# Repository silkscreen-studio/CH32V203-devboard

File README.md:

# CH32V203 devboard

A simple CH32V203C8U6 devboard, with a 7x8 charlieplexed matrix and a 12P FPC for IOs, beside the more common 2.54 headers for breadboard compatibility.
<br></br>

# Key features 
 - CH32V203C8U6 MCU:
    - FLASH: 64k (+224K non-zero-wait program memory)
    - SRAM: 20k
    - 144MHz CPU max clock speed
    - 37 GPIOs
    - Many peripherals (4x USART, 2x SPI, 2x I2C, 1x CAN, USB (FS))
    - 9 analog capable GPIOs
    - 12 PWM capable GPIOs
 - USB-C for programming, USB device/host emulation, and power
 - 7x8 charlieplexed LED matrix (8 GPIOs)
 - 23x 2.54mm header pins
 - 12P .5mm FPC for breaking out 9 more IOs
 - Boot and Reset Button
 - On board 3.3V LDO `TLV75733PDBVR`, 1A max current

Demo with the charlieplexed LED matrix in action:
https://youtube.com/shorts/uVbg5wJzLvo
<br></br>

<br></br>

# Schematic

<br></br>

# PCB layout

<br></br>

# Pinout

<br></br>

# BOM

| Qty | Type | Part | Value | Extended description | Unit price | Price [MOQ]| LCSC part number | Link |
| --- | --- | --- | --- | --- | --- | --- | --- | --- |
| 7 | MLCC | CL05B104KB54PNC | 100nF | 0402 | $0.014 | $1.40 [100] | C307331 | https://www.lcsc.com/product-detail/C307331.html |
| 3 | MLCC | CL10A106MA8NRNC | 10µF | 0603 | $0.14 | $2.80 [20] | C96446 | https://www.lcsc.com/product-detail/C96446.html |
| 1 | Ideal Diode | CH213K | |  | $0.074 | $0.74 [10] | C5456874 | https://www.lcsc.com/product-detail/C5456874.html |
| 1 | FPC connector 12P | FPC-05F-12PH20 | |  | $0.11 | $0.57 [5] | C2856799 | https://www.lcsc.com/product-detail/C2856799.html |
| 56 | LED | XL-1005UOC | | Orange 0402 LED | $0.014 | $1.42 [100] | C965791 | https://www.lcsc.com/product-detail/C965791.html |
| 3 | Resistor | RC0402JR-7W10KL | 10k | 0402 SMD resistor | $0.004 | $0.45 [100] | C851859 | https://www.lcsc.com/product-detail/C851859.html |
| 2 | Resistor | RC-02K512JT | 5.1k | 0402 SMD resistor | $0.0033 | $0.33 [100] | C453708 | https://www.lcsc.com/product-detail/C453708.html |
| 8 | Resistor | RC0402FR-07680RL | 680 | 0402 SMD resistor | $0.0014 | $0.14 [100] | C137948 | https://www.lcsc.com/product-detail/C137948.html |
| 2 | Push button | TS-1075S-A1B2-D4 | | | $0.066 | $0.66 [10] | C492872 | https://www.lcsc.com/product-detail/C492872.html |
| 1 | MCU | CH32V203C8U6 | | | $0.85 | $0.85 [1] | C6407762 | https://www.lcsc.com/product-detail/C6407762.html |
| 1 | LDO | TLV75733PDBVR | | 3.3V LDO | $0.18 | $0.92 [5] | C485517 | https://www.lcsc.com/product-detail/C485517.html |
| 1 | ESD protection | USBLC6-2P6 | | | $0.28 | $1.39 [5] | C15999 | https://www.lcsc.com/product-detail/C15999.html |
| 1 | PCB | | | | $5 |  |  | https://jlcpcb.com/quote |
|  |  |  |  |  |  |  |  |  |
|  | TOTAL (price per board) | | | | $7.96 |  |  |  |
|  | TOTAL (price due to MOQ) | | | | $16.67 |  |  |  |

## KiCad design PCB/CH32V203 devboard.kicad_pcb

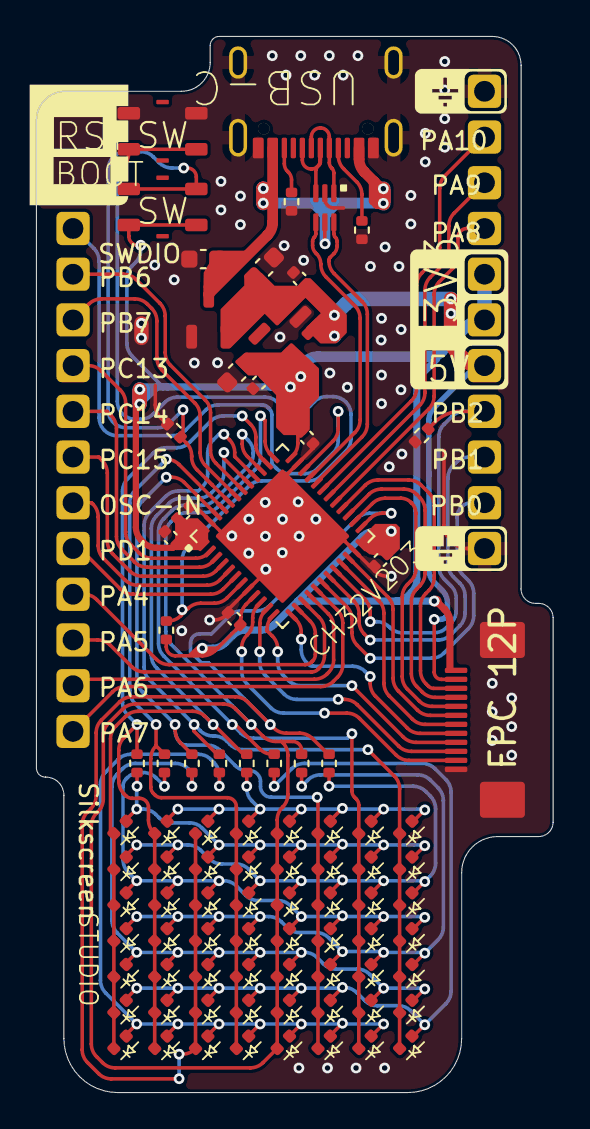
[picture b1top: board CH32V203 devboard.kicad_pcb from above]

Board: 2 copper layers, 28.7 x 58.7 mm, 110 parts (0 on the bottom side), 55 nets.

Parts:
C1, C2, C3, C4, C5, C6, C9: 100nF; C_0402_1005Metric
C7, C8, C10: 10uF; C_0603_1608Metric
D1: SOT-23-3
FPC1: FPC 12P Custom footprint C2856799
J1: USB C connector USB2.0 16P; USB_C_16P_custom_footprint_C2765186
LED2, LED3, LED4, LED5, LED6, LED7, LED8, LED9, LED11, LED12, LED13, LED14, LED15, LED16, LED17, LED18, LED20, LED21, LED22, LED23, LED24, LED25, LED26, LED27, LED29, LED30, LED31, LED32, LED33, LED34, LED35, LED36, LED38, LED39, LED40, LED41, LED42, LED43, LED44, LED45, LED47, LED48, LED49, LED50, LED51, LED52, LED53, LED54, LED56, LED57, LED58, LED59, LED60, LED61, LED62, LED63: LED; CUSTOM LED_0402_1005Metric
P1, P2, P3, P4, P5, P6, P7, P8, P9, P10, P12, P13, P18, P19, P20, P21, P22, P23, P26, P27, P28, P29, P30: Custom 1P 2.54mm header
R1, R2, R3: 10k; R_0402_1005Metric
R4, R5: 5.1k; R_0402_1005Metric
R6, R7, R8, R9, R10, R11, R12, R13: 680; R_0402_1005Metric
SW1, SW2: SW_Push; switch_custom_footprint_TS-1075S-A1B2-D4_C492872.pretty
U1: CUSTOM_QFN-48-1EP_7x7mm_P0.5mm_EP5.3x5.3mm
U2: SOT-23-5
U3: USBLC6-2P6; USB ESD SOT666 C15999

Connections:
+3.3V: C1.1, C2.1, C3.1, C4.1, C5.1, C8.1, C9.1, FPC1.1, P18.1, P19.1, R1.1, SW2.2, U1.1 (VBAT), U1.9 (VDDA), U1.24 (VDD_VIO_1), U1.36 (VDD_2), U1.48 (VDD_VIO_3), U2.5 (OUT)
+5V: C6.1, C7.1, D1.2 (OUT+), FPC1.2, P20.1, U2.1 (IN), U2.3 (EN)
/USB.VBUS: C10.1, D1.3 (IN+), J1.VBUS (VBUS_VBUS), U3.5 (VBUS)
GND: C1.2, C2.2, C3.2, C4.2, C5.2, C6.2, C7.2, C8.2, C9.2, C10.2, D1.1 (GND), FPC1.12, FPC1.13 (SH1), FPC1.14 (SH2), J1.GND (GND_GND), J1.SHIELD (SHIELD_SH), P12.1, P13.1, R2.2, R3.2, R4.2, R5.2, SW1.1, U1.8 (VSSA), U1.23 (VSS_1), U1.35 (VSS_2), U1.47 (VSS_3), U1.49 (VSS), U2.2 (GND), U3.2 (GND)
unnamed: J1.CC1 (CC1_CC1), R5.1
unnamed: J1.CC2 (CC2_CC2), R4.1
unnamed: J1.D+ (D+_D+), U3.3 (I/O2)
unnamed: J1.D- (D-_D-), U3.1 (I/O1)
unnamed: LED3.2 (A), LED11.2 (A), LED27.2 (A), LED35.2 (A), LED43.2 (A), LED51.2 (A), LED59.2 (A), R8.2
unnamed: LED4.2 (A), LED12.2 (A), LED20.2 (A), LED36.2 (A), LED44.2 (A), LED52.2 (A), LED60.2 (A), R9.2
unnamed: LED5.2 (A), LED13.2 (A), LED21.2 (A), LED29.2 (A), LED45.2 (A), LED53.2 (A), LED61.2 (A), R10.2
unnamed: LED6.2 (A), LED14.2 (A), LED22.2 (A), LED30.2 (A), LED38.2 (A), LED54.2 (A), LED62.2 (A), R11.2
unnamed: LED7.2 (A), LED15.2 (A), LED23.2 (A), LED31.2 (A), LED39.2 (A), LED47.2 (A), LED63.2 (A), R12.2
unnamed: LED8.2 (A), LED16.2 (A), LED24.2 (A), LED32.2 (A), LED40.2 (A), LED48.2 (A), LED56.2 (A), R13.2
unnamed: LED9.2 (A), LED17.2 (A), LED25.2 (A), LED33.2 (A), LED41.2 (A), LED49.2 (A), LED57.2 (A), R6.2
unnamed: LED2.2 (A), LED18.2 (A), LED26.2 (A), LED34.2 (A), LED42.2 (A), LED50.2 (A), LED58.2 (A), R7.2
unnamed: R2.1, SW2.1, U1.44 (BOOT0)
unnamed: R1.2, SW1.2, U1.7 (NRST)
OSC_IN: P4.1, U1.5 (OSC_IN/PD0)
PA0: FPC1.11, U1.10 (PA0/WKUP/ADC0/TIM2_CH1)
PA1: FPC1.10, U1.11 (PA1/ADC1/TIM2_CH2)
PA2: FPC1.9, U1.12 (PA2/ADC2/TIM2_CH3/TX2)
PA3: FPC1.8, U1.13 (PA3/ADC3/TIM2_CH4/RX2)
PA4: P6.1, U1.14 (PA4/ADC4)
PA5: P7.1, U1.15 (PA5/ADC5/SPI1_SCK)
PA6: P8.1, U1.16 (PA6/ADC6/SPI1_MISO/TIM3_CH1)
PA7: P9.1, U1.17 (PA7/ADC7/SPI1_MOSI/TIM3_CH2)
PA8: P26.1, U1.29 (TIM1_CH1/PA8)
PA9: P27.1, U1.30 (TX1/TIM1_CH2/PA9)
PA10: P28.1, U1.31 (RX1/TIM1_CH3/PA10)
PA14: LED33.1 (K), LED34.1 (K), LED35.1 (K), LED36.1 (K), LED38.1 (K), LED39.1 (K), LED40.1 (K), R10.1, U1.37 (SWCLK/PA14)
PA15: LED9.1 (K), LED11.1 (K), LED12.1 (K), LED13.1 (K), LED14.1 (K), LED15.1 (K), LED16.1 (K), R7.1, U1.38 (PA15)
PB0: P21.1, U1.18 (PB0/ADC8/TIM3_CH3/TX4)
PB1: P22.1, U1.19 (PB1/ADC9/TIM3_CH4/RX4)
PB2/BOOT1: P10.1, R3.1, U1.20 (PB2/BOOT1)
PB3: LED49.1 (K), LED50.1 (K), LED51.1 (K), LED52.1 (K), LED53.1 (K), LED54.1 (K), LED56.1 (K), R12.1, U1.39 (PB3)
PB4: LED57.1 (K), LED58.1 (K), LED59.1 (K), LED60.1 (K), LED61.1 (K), LED62.1 (K), LED63.1 (K), R13.1, U1.40 (PB4)
PB5: LED2.1 (K), LED3.1 (K), LED4.1 (K), LED5.1 (K), LED6.1 (K), LED7.1 (K), LED8.1 (K), R6.1, U1.41 (PB5)
PB6: P29.1, U1.42 (TIM4_CH1/SCL1/PB6/USB2DM)
PB7: P30.1, U1.43 (TIM4_CH2/SDA1/PB7/USB2DP)
PB8: LED25.1 (K), LED26.1 (K), LED27.1 (K), LED29.1 (K), LED30.1 (K), LED31.1 (K), LED32.1 (K), R9.1, U1.45 (TIM4_CH3/PB8)
PB9: LED41.1 (K), LED42.1 (K), LED43.1 (K), LED44.1 (K), LED45.1 (K), LED47.1 (K), LED48.1 (K), R11.1, U1.46 (TIM4_CH4/PB9)
PB10: FPC1.7, U1.21 (PB10/SCL2/TX3)
PB11: FPC1.6, U1.22 (PB11/SDA2/RX3)
PB12: LED17.1 (K), LED18.1 (K), LED20.1 (K), LED21.1 (K), LED22.1 (K), LED23.1 (K), LED24.1 (K), R8.1, U1.25 (PB12)
PB13: FPC1.5, U1.26 (SPI2_SCK/PB13)
PB14: FPC1.4, U1.27 (SPI2_MISO/PB14)
PB15: FPC1.3, U1.28 (SPI2_MOSI/PB15)
PC13: P1.1, U1.2 (PC13/TAMPER_RTC)
PC14: P2.1, U1.3 (PC14/OSC32IN)
PC15: P3.1, U1.4 (PC15/OSC32OUT)
PD1: P5.1, U1.6 (OSC_OUT/PD1)
SWDIO: P23.1, U1.34 (SWDIO/PA13)
USB.D+: U1.33 (CAN_TX1/PA12/USB1DP), U3.4 (I/O2)
USB.D-: U1.32 (TIM1_CH4/CAN_RX1/PA11/USB1DM), U3.6 (I/O1)
